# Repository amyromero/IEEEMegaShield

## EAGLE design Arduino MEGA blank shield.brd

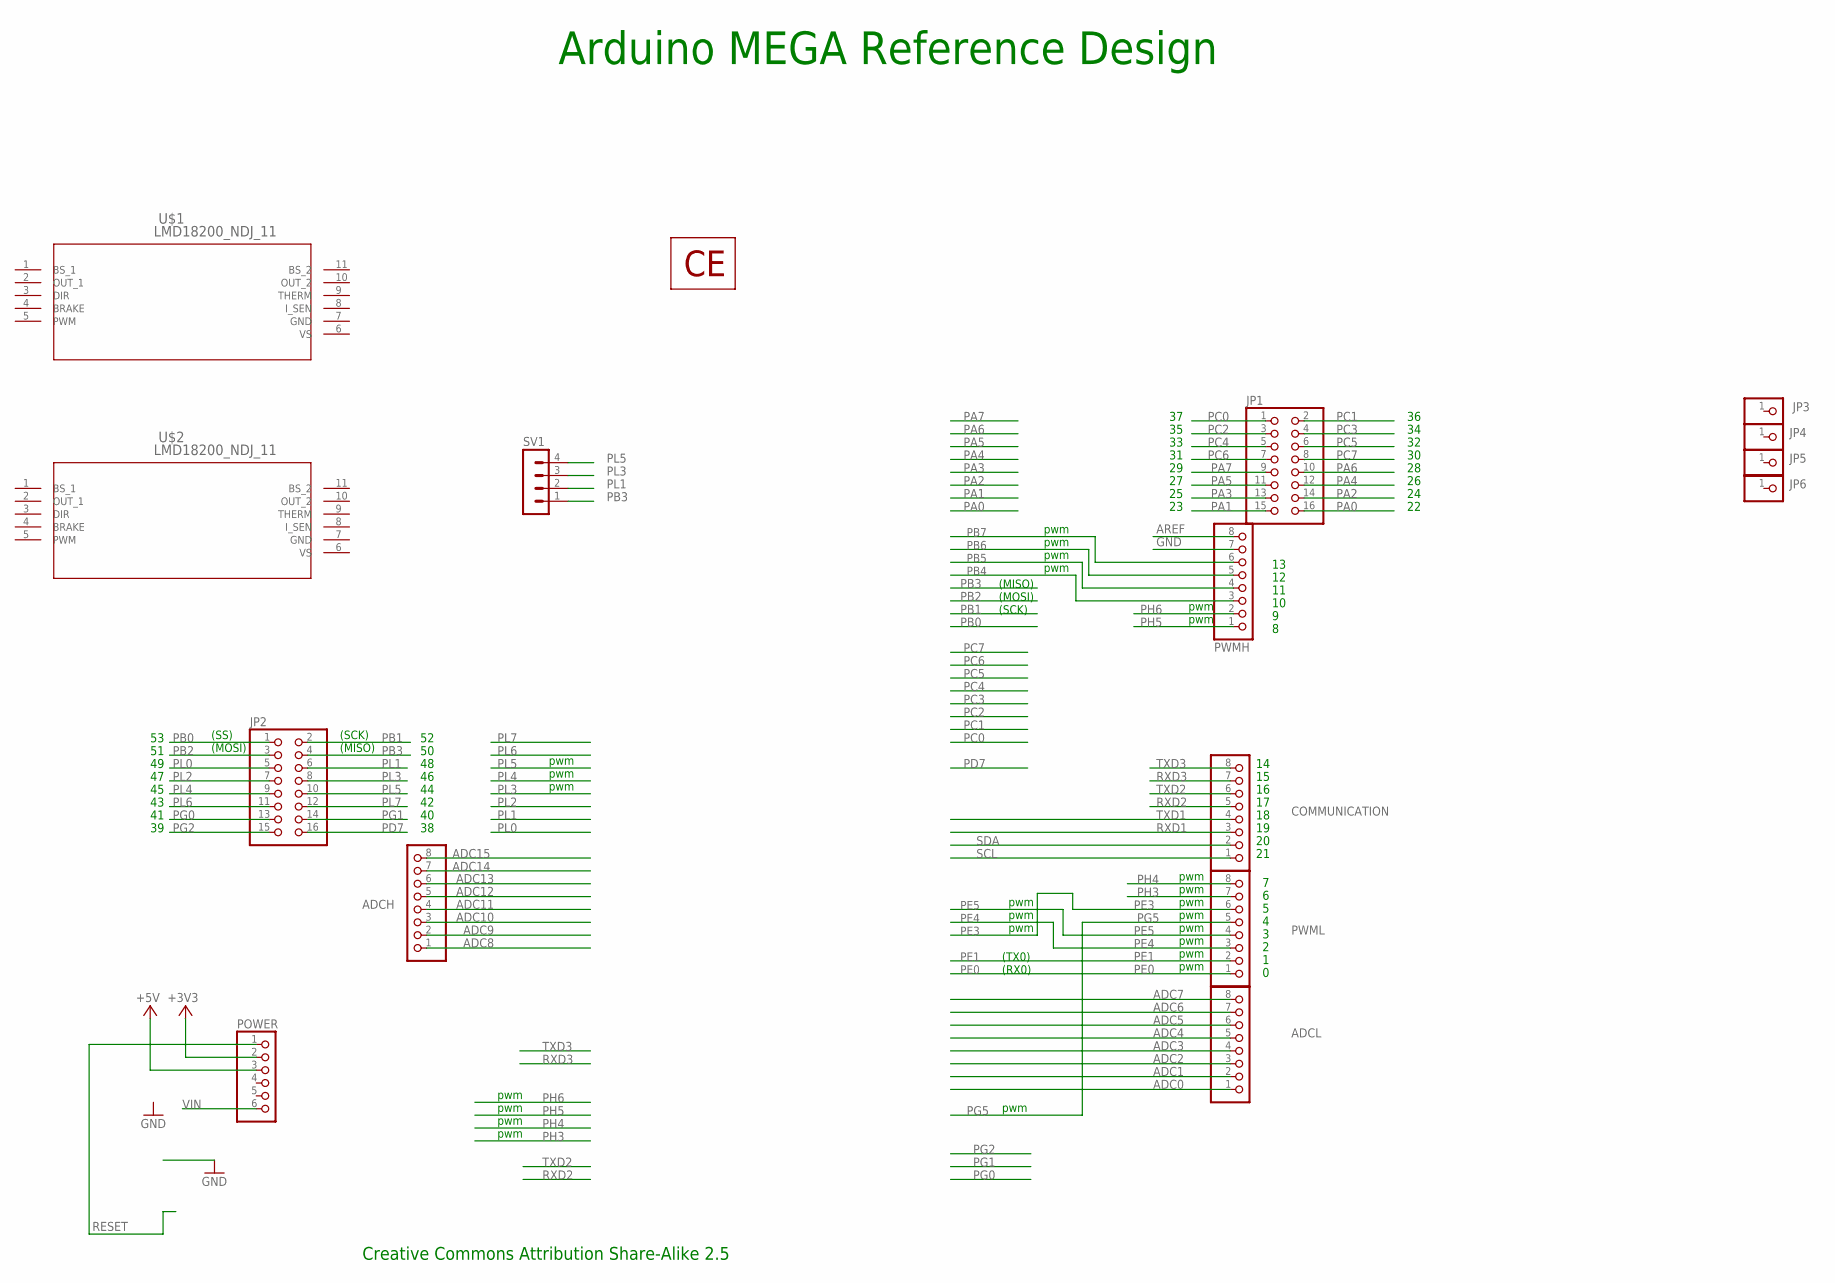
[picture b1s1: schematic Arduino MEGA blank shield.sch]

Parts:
ADCH: PINHD-1X8; 1X08
ADCL: PINHD-1X8; 1X08
COMMUNICATION: PINHD-1X8; 1X08
JP1, JP2: PINHD-2X8; 2X08
JP3, JP4, JP5, JP6: PINHD-1X1; 1X01
POWER: PINHD-1X6; 1X06
PWMH: PINHD-1X8; 1X08
PWML: PINHD-1X8; 1X08
SV1: MA04-1
U$1, U$2: LMD18200_NDJ_11; TA11B
U$4: CE; CE-COPPER

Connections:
+3V3: POWER.2
+5V: POWER.3
ADC0: ADCL.1
ADC1: ADCL.2
ADC2: ADCL.3
ADC3: ADCL.4
ADC4: ADCL.5
ADC5: ADCL.6
ADC6: ADCL.7
ADC7: ADCL.8
ADC8: ADCH.1
ADC9: ADCH.2
ADC10: ADCH.3
ADC11: ADCH.4
ADC12: ADCH.5
ADC13: ADCH.6
ADC14: ADCH.7
ADC15: ADCH.8
AREF: PWMH.8
GND: PWMH.7, U$1.7 (GND), U$2.7 (GND)
PA0: JP1.16
PA1: JP1.15
PA2: JP1.14
PA3: JP1.13
PA4: JP1.12
PA5: JP1.11
PA6: JP1.10
PA7: JP1.9
PB0: JP2.1
PB1: JP2.2
PB2: JP2.3
PB3: JP2.4, SV1.1
PB4: PWMH.3
PB5: PWMH.4
PB6: PWMH.5
PB7: PWMH.6
PC0: JP1.1
PC1: JP1.2
PC2: JP1.3
PC3: JP1.4
PC4: JP1.5
PC5: JP1.6
PC6: JP1.7
PC7: JP1.8
PD7: JP2.16
PE0: PWML.1
PE1: PWML.2
PE3: PWML.6
PE4: PWML.3
PE5: PWML.4
PG0: JP2.13
PG1: JP2.14
PG2: JP2.15
PG5: PWML.5
PH3: PWML.7
PH4: PWML.8
PH5: PWMH.1
PH6: PWMH.2
PL0: JP2.5
PL1: JP2.6, SV1.2
PL2: JP2.7
PL3: JP2.8, SV1.3
PL4: JP2.9
PL5: JP2.10, SV1.4
PL6: JP2.11
PL7: JP2.12
RESET: POWER.1
RXD1: COMMUNICATION.3
RXD2: COMMUNICATION.5
RXD3: COMMUNICATION.7
SCL: COMMUNICATION.1
SDA: COMMUNICATION.2
TXD1: COMMUNICATION.4
TXD2: COMMUNICATION.6
TXD3: COMMUNICATION.8
VIN: POWER.6
VS: U$1.6 (VS), U$2.6 (VS)

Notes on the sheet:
Arduino MEGA Reference Design
pwm
(TX0)
(RX0)
(MISO)
(SCK)
(MOSI)
(SS)
Creative Commons Attribution Share-Alike 2.5

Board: 2 copper layers, 16 parts (1 on the bottom side), 6 nets, no tracks yet.

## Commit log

2014-03-29 added dummy part for git demo
2014-03-29 removed dummy part
2014-03-29 real addition of header
2014-03-29 added motor controls
2014-04-16 headers added and LMD18200t circuit added
